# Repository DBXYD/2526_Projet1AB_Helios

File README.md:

# 2526_Projet1AB_Helios
Projet de 1ère année ENSEA sur un stroboscobe RGB
## Sommaire
* [Cahier des charges](#cahier-des-charges)
* [Matériels utilisés](#matériels-utilisés)
* [Organisation du projet](#organisation-du-projet)
  * [Architecture PCB](#architecture-pcb)
* [Journal de Bord du projet](#journal-de-bord-du-projet)
* [Répartition des Tâches](#répartition-des-tâches)
* [Membres du projet](#membres-du-projet)
## Cahier des charges
**Project scénique à LED**
* Strobe RGBW haute puissance (100 W minimum)
* Pilotage DMX512 (standard éclairage)
* interface utilisateur intuitive
* Modifier la fréquence d'allumage des LEDs
* Modes :
    * Intensité R/G/B
    * Strobe (fréquence, intensité)
* Sécurité thermique + électrique

**Contraintes**
* Alimentation secteur
* Fiabilité (usage scène)
* Dissipation thermique sérieuse
* Respect du DMX (isolation, timing)

## Présentation du projet
* [Présentation Hardware](https://github.com/DBXYD/2526_Projet1AB_Helios/blob/master/Presentation/Projet%201AB%20-%20H%C3%A9lios.pdf)
* [Architecture du Code](https://github.com/DBXYD/2526_Projet1AB_Helios/blob/master/Presentation/Projet1AB_Helios_Code.pdf) (DMX 512)

## Diagrammes
* [Diagrammes](https://github.com/DBXYD/2526_Projet1AB_Helios/tree/master/Presentation/Diagrammes)

## Matériels utilisés
| **Composant** | **Référence** |
| :-------- | :-------- |
| LEDs 98 (x3 couleurs) | [150505M173300](https://github.com/DBXYD/2526_Projet1AB_Helios/blob/master/datasheet/Datasheets%20du%20projet/LED_150505M173300.pdf) |
| 6 Driver | [LM3404](https://github.com/DBXYD/2526_Projet1AB_Helios/blob/master/datasheet/Datasheets%20du%20projet/lm3404.pdf) |
| Microcontrolleur | [STM32F103C6T6A LQFP-48](https://github.com/DBXYD/2526_Projet1AB_Helios/blob/master/datasheet/Datasheets%20du%20projet/stm32f103c6.pdf) |
| DMX512 | Mâle: [NC3MAAH](https://github.com/DBXYD/2526_Projet1AB_Helios/blob/master/datasheet/Datasheets%20du%20projet/nc3maah(DMX512M).pdf) Femelle: [NC3FAAH](https://github.com/DBXYD/2526_Projet1AB_Helios/blob/master/datasheet/Datasheets%20du%20projet/nc3faah(DMX512F).pdf) |
| Power Module WPME-FDSM | [173950536](https://github.com/DBXYD/2526_Projet1AB_Helios/blob/master/datasheet/Datasheets%20du%20projet/Power_Module_WPME-FDSM_173950536.pdf) |
| LOW DROPOUT LINEAR REGULATOR | [AZ1117CH2-TRG1](https://github.com/DBXYD/2526_Projet1AB_Helios/blob/master/datasheet/Datasheets%20du%20projet/AZ1117CH2-3.3TRG1.pdf) | 
| Ecran OLED | [OLED Dipslay](https://github.com/DBXYD/2526_Projet1AB_Helios/blob/master/datasheet/Datasheets%20du%20projet/SBC-OLED01_Datasheet_2022-01-06.pdf) |
| Alimentation | 24V / 5A | 
| Résistances | 2 x 1 kΩ ; 5 x 10 kΩ ; 2 x 1,6 kΩ ; 6 x 100 kΩ |
| Inductances | 6 x 18 uH |
| Condensateurs | 18 x 100 nF ; 2 x 1 uF ; 3 x 10 uF ; 1 x 22 uF ; 2 x 10 nF |
| LEDs SMD | 2 x [LED_0805_2012Metric](https://github.com/DBXYD/2526_Projet1AB_Helios/blob/master/datasheet/Datasheets%20du%20projet/LED_0805_2012Metric.pdf) |
| Boutons poussoirs | 3 x [Bouton ](https://github.com/DBXYD/2526_Projet1AB_Helios/blob/master/datasheet/Datasheets%20du%20projet/6x6_mm_sw_switches.pdf) |
| Puce MAX485E | [Puce](https://github.com/DBXYD/2526_Projet1AB_Helios/blob/master/datasheet/Datasheets%20du%20projet/MAX1487E-MAX491E.pdf) |
| Connecteur AMASS | [Connecteur 1](https://github.com/DBXYD/2526_Projet1AB_Helios/blob/master/datasheet/Datasheets%20du%20projet/XT30U-M_AMASS_Datasheet.pdf)|
| Connecteur PinHeader | [Connecteur 2](https://github.com/DBXYD/2526_Projet1AB_Helios/blob/master/datasheet/Datasheets%20du%20projet/connecteur%20pinheader.pdf)|

## Organisation du projet

### Architecture PCB:
* **Alimentation** : Power Module WPME-FSDM, AZ1117CH2-TRG1
* **Contrôle** : Microcontrolleur avec interface OLED
* **Pilotage LEDs** : drivers pour les chaînes R, G, B (2 drivers par couleur)
* **Protection et sécurité** : TODO (fusible, dissipateurs thermiques, diode)

### BOM:
[Matériel utilisé](https://github.com/DBXYD/2526_Projet1AB_Helios/blob/master/Hardware/KICAD_HELIOS/bom/ibom.html)

## Journal de Bord du projet 
[Journal de Bord](https://github.com/DBXYD/2526_Projet1AB_Helios/blob/master/journal_de_bord.md)

## Répartition des Tâches
| **Nom Prénom** | **Tâche(s)** |
| :-------- | :-------- |
| **TRITON Kylian** | Schématique du PCB, Routage du PCB, Valeurs des composants (fichier python), Mise à jour du Github, Recherche des composants |
| **RIEU Pierric** | Software des drivers (intégralité des codes), PCB |
| **BAILLEUL Sara** | Soudage, Vérification des empreintes sur PCB, Commande des composants et bon de commande du PCB, Recherche des composants (soudage et datasheet), Mise à jour du GitHub, Diagramme Hardware |
| **LEIRAS Clara** | LEDs (Schématique du PCB), Soudage, Recherche des composants (datasheet) |
| **GOMRI Samuel** | Recherche des composants |

## Membres du projet
|   |   |   |   |   |
|:---:|:---:|:---:|:---:|:---:|
|  |  |  |  |  | 
| [**@TritonKylian**](https://github.com/TritonKylian)<br>TRITON Kylian| [**@PierricRieu**](https://github.com/PierricRieu)<br>RIEU Pierric | [**@sblikeice**](https://github.com/sblikeice)<br> BAILLEUL Sara | [**@claralrs9**](https://github.com/claralrs9)<br>LEIRAS Clara| [**@sgomri**](https://github.com/sgomri)<br>GOMRI Samuel |

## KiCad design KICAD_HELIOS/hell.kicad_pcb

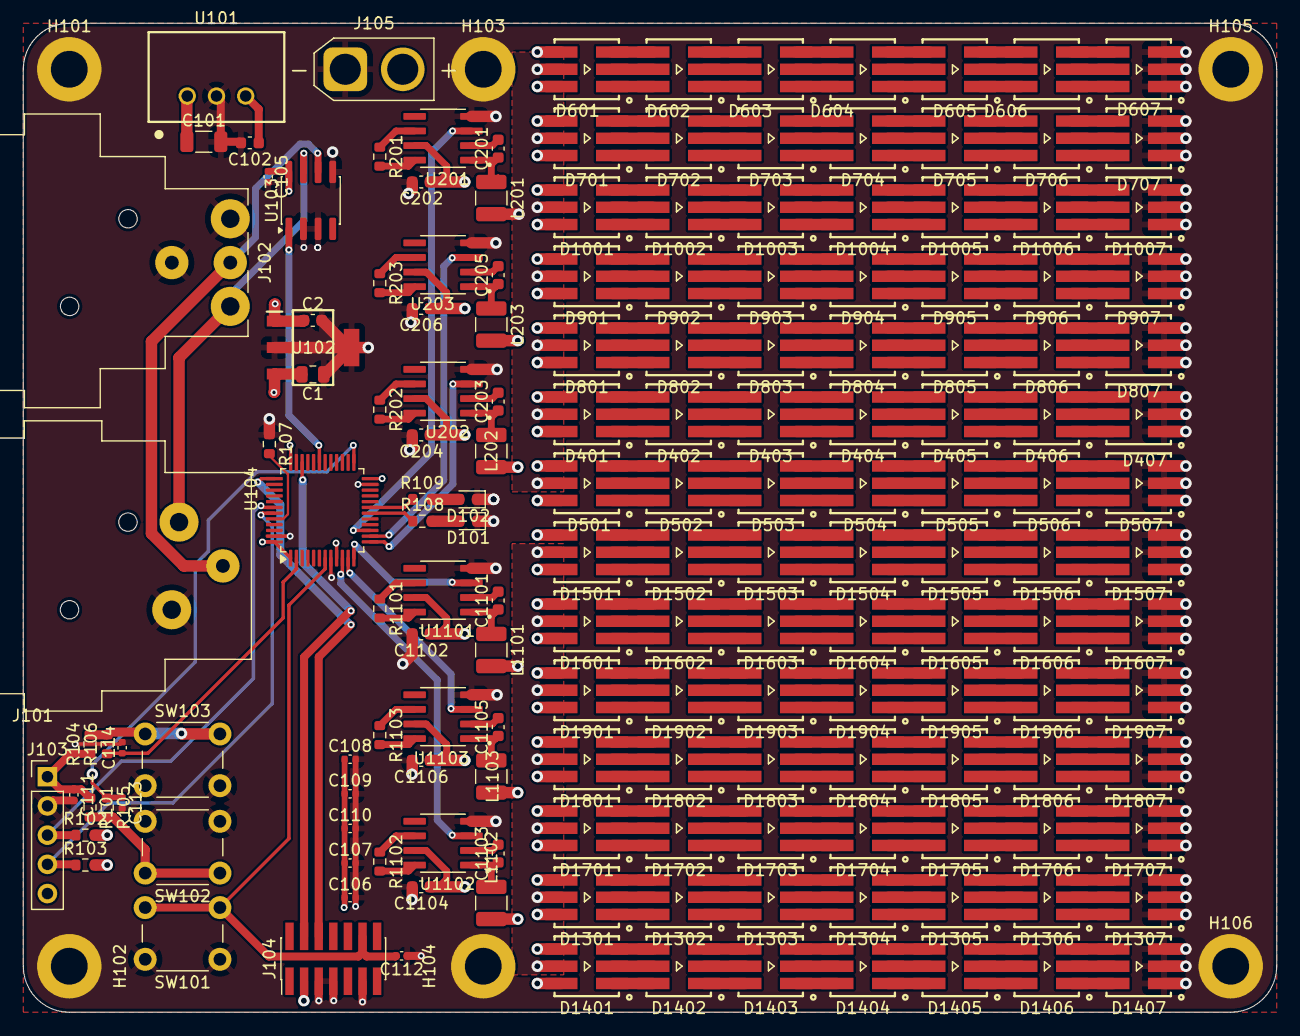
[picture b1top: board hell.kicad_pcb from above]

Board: 4 copper layers, 109.0 x 86.0 mm, 171 parts (0 on the bottom side), 309 nets.

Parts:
C1: 22u; C_0805_2012Metric
C2, C102: 10u; C_0603_1608Metric
C101: 10u; C_1206_3216Metric
C105, C107, C108, C109, C110, C112: 100n; C_0402_1005Metric
C106, C111: 1u; C_0402_1005Metric
C113, C114: 10n; C_0402_1005Metric
C201, C202, C203, C204, C205, C206, C1101, C1102, C1103, C1104, C1105, C1106: 100n; C_0603_1608Metric
D101, D102: LED; LED_0603_1608Metric
D401, D402, D403, D404, D405, D406, D407, D501, D502, D503, D504, D505, D506, D507, D601, D602, D603, D604, D605, D606, D607, D701, D702, D703, D704, D705, D706, D707, D801, D802, D803, D804, D805, D806, D807, D901, D902, D903, D904, D905, D906, D907, D1001, D1002, D1003, D1004, D1005, D1006, D1007, D1301, D1302, D1303, D1304, D1305, D1306, D1307, D1401, D1402, D1403, D1404, D1405, D1406, D1407, D1501, D1502, D1503, D1504, D1505, D1506, D1507, D1601, D1602, D1603, D1604, D1605, D1606, D1607, D1701, D1702, D1703, D1704, D1705, D1706, D1707, D1801, D1802, D1803, D1804, D1805, D1806, D1807, D1901, D1902, D1903, D1904, D1905, D1906, D1907: WL-SFTW_5050_PLCC6
H101, H102, H103, H104, H105, H106: MountingHole_Pad; MountingHole_3.2mm_M3_DIN965_Pad
J101: NC3FAAH; Jack_XLR_Neutrik_NC3FAAH_Horizontal
J102: NC3MAAH; Jack_XLR_Neutrik_NC3MAAH_Horizontal
J103: ecran; PinHeader_1x05_P2.54mm_Vertical
J104: Conn_ST_STDC14; PinHeader_2x07_P1.27mm_Vertical_SMD
J105: Conn_01x02; AMASS_XT30U-M_1x02_P5.0mm_Vertical
L201, L202, L203, L1101, L1102, L1103: 18u; L_1210_3225Metric
R101, R104, R105, R106, R107: 10k; R_0603_1608Metric
R102, R103: 1k; R_0603_1608Metric
R108, R109: 1k6; R_0603_1608Metric
R201, R202, R203, R1101, R1102, R1103: 100k; R_0603_1608Metric
SW101, SW102, SW103: SW_Push; SW_PUSH_6mm
U101: R-78B5.0-2.0; WPME-FDSM_173950536
U102: AZ1117CH2-3.3TRG1; SOT230P700X180-4N
U103: MAX485E; SOIC-8_3.9x4.9mm_P1.27mm
U104: STM32F103C6Tx; LQFP-48_7x7mm_P0.5mm
U201, U202, U203, U1101, U1102, U1103: LM3404MA; SOIC127P599X175-8N

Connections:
+3.3V: C1.2, C106.1, C107.1, C108.1, C109.1, C110.1, C111.1, J103.1, J104.3 (VCC), R101.1, R102.2, R103.2, R104.1, U102.3 (OUTPUT), U104.1 (VBAT), U104.9 (VDDA), U104.24 (VDD), U104.36 (VDD), U104.48 (VDD)
+5V: C2.1, C102.1, C105.1, U101.3, U102.1 (INPUT), U103.8 (VCC)
+24V: C101.1, C202.1, C204.1, C206.1, C1102.1, C1104.1, C1106.1, J105.2, U101.1, U201.7 (VCC), U202.7 (VCC), U203.7 (VCC), U1101.7 (VCC), U1102.7 (VCC), U1103.7 (VCC)
/Driver_49LED_RGB_1/B_49_Anode: D401.2, D501.2, D601.2, D701.2, D801.2, D901.2, D1001.2, L203.2
/Driver_49LED_RGB_1/G_49_Anode: D401.6, D501.6, D601.6, D701.6, D801.6, D901.6, D1001.6, L202.2
/Driver_49LED_RGB_1/R_49_Anode: D401.4, D501.4, D601.4, D701.4, D801.4, D901.4, D1001.4, L201.2
/Driver_49LED_RGB_2/B_49_Anode: D1301.2, D1401.2, D1501.2, D1601.2, D1701.2, D1801.2, D1901.2, L1103.2
/Driver_49LED_RGB_2/G_49_Anode: D1301.6, D1401.6, D1501.6, D1601.6, D1701.6, D1801.6, D1901.6, L1102.2
/Driver_49LED_RGB_2/R_49_Anode: D1301.4, D1401.4, D1501.4, D1601.4, D1701.4, D1801.4, D1901.4, L1101.2
BOUTTON_1: C114.1, R106.1, U104.2 (PC13)
BOUTTON_2: C113.1, R105.1, U104.25 (PB12)
DMX_N: J101.2, J102.2, U103.7 (B)
DMX_P: J101.3, J102.3, U103.6 (A)
DMX_RX: U103.1 (RO), U104.31 (PA10)
Ecr_SCL: J103.3, R102.1, U104.42 (PB6)
Ecr_SDA: J103.4, R103.1, U104.43 (PB7)
GND: C1.1, C2.2, C101.2, C102.2, C105.2, C106.2, C107.2, C108.2, C109.2, C110.2, C111.2, C112.1, C113.2, C114.2, C202.2, C204.2, C206.2, C1102.2, C1104.2, C1106.2, D101.1 (K), D102.1 (K), D407.1, D407.3, D407.5, D507.1, D507.3, D507.5, D607.1, D607.3, D607.5, D707.1, D707.3, D707.5, D807.1, D807.3, D807.5, D907.1, D907.3, D907.5, D1007.1, D1007.3, D1007.5, D1307.1, D1307.3, D1307.5, D1407.1, D1407.3, D1407.5, D1507.1, D1507.3, D1507.5, D1607.1, D1607.3, D1607.5, D1707.1, D1707.3, D1707.5, D1807.1, D1807.3, D1807.5, D1907.1, D1907.3, D1907.5, H101.1, H102.1, H103.1, H104.1, H105.1, H106.1, J101.1, J102.1, J102.G, J103.2, J104.5 (GND), J104.7 (GND), J104.11 (GNDDetect), J105.1, R107.1, SW101.1, SW102.2, SW103.2, U101.2, U102.2 (ADJ/GND_1), U102.4 (ADJ/GND_2), U103.2 (~RE), U103.3 (DE), U103.5 (GND), U104.8 (VSSA), U104.23 (VSS), U104.35 (VSS), U104.47 (VSS), U201.4 (GND), U202.4 (GND), U203.4 (GND), U1101.4 (GND), U1102.4 (GND), U1103.4 (GND)
LEDB1: U104.14 (PA4), U203.3 (DIM)
LEDB2: U104.11 (PA1), U1103.3 (DIM)
LEDG1: U104.13 (PA3), U202.3 (DIM)
LEDG2: U104.10 (PA0), U1102.3 (DIM)
LEDR1: U104.15 (PA5), U201.3 (DIM)
LEDR2: U104.12 (PA2), U1101.3 (DIM)
LED_1: R108.1, U104.18 (PB0)
LED_2: R109.1, U104.19 (PB1)
NRST: C112.2, J104.12 (~RST), SW101.2, U104.7 (NRST)
unnamed: D101.2 (A), R108.2
unnamed: D102.2 (A), R109.2
unnamed: D401.1, D402.2
unnamed: D401.3, D402.4
unnamed: D401.5, D402.6
unnamed: D402.1, D403.2
unnamed: D402.3, D403.4
unnamed: D402.5, D403.6
unnamed: D403.1, D404.2
unnamed: D403.3, D404.4
unnamed: D403.5, D404.6
unnamed: D404.1, D405.2
unnamed: D404.3, D405.4
unnamed: D404.5, D405.6
unnamed: D405.1, D406.2
unnamed: D405.3, D406.4
unnamed: D405.5, D406.6
unnamed: D406.1, D407.2
unnamed: D406.3, D407.4
unnamed: D406.5, D407.6
unnamed: D501.1, D502.2
unnamed: D501.3, D502.4
unnamed: D501.5, D502.6
unnamed: D502.1, D503.2
unnamed: D502.3, D503.4
unnamed: D502.5, D503.6
unnamed: D503.1, D504.2
unnamed: D503.3, D504.4
unnamed: D503.5, D504.6
unnamed: D504.1, D505.2
unnamed: D504.3, D505.4
unnamed: D504.5, D505.6
unnamed: D505.1, D506.2
unnamed: D505.3, D506.4
unnamed: D505.5, D506.6
unnamed: D506.1, D507.2
unnamed: D506.3, D507.4
unnamed: D506.5, D507.6
unnamed: D601.1, D602.2
unnamed: D601.3, D602.4
unnamed: D601.5, D602.6
unnamed: D602.1, D603.2
unnamed: D602.3, D603.4
unnamed: D602.5, D603.6
unnamed: D603.1, D604.2
unnamed: D603.3, D604.4
unnamed: D603.5, D604.6
unnamed: D604.1, D605.2
unnamed: D604.3, D605.4
unnamed: D604.5, D605.6
unnamed: D605.1, D606.2
unnamed: D605.3, D606.4
unnamed: D605.5, D606.6
unnamed: D606.1, D607.2
unnamed: D606.3, D607.4
unnamed: D606.5, D607.6
unnamed: D701.1, D702.2
unnamed: D701.3, D702.4
unnamed: D701.5, D702.6
unnamed: D702.1, D703.2
unnamed: D702.3, D703.4
unnamed: D702.5, D703.6
unnamed: D703.1, D704.2
unnamed: D703.3, D704.4
unnamed: D703.5, D704.6
unnamed: D704.1, D705.2
unnamed: D704.3, D705.4
unnamed: D704.5, D705.6
unnamed: D705.1, D706.2
unnamed: D705.3, D706.4
unnamed: D705.5, D706.6
unnamed: D706.1, D707.2
unnamed: D706.3, D707.4
unnamed: D706.5, D707.6
unnamed: D801.1, D802.2
unnamed: D801.3, D802.4
unnamed: D801.5, D802.6
unnamed: D802.1, D803.2
unnamed: D802.3, D803.4
unnamed: D802.5, D803.6
unnamed: D803.1, D804.2
unnamed: D803.3, D804.4
unnamed: D803.5, D804.6
unnamed: D804.1, D805.2
unnamed: D804.3, D805.4
unnamed: D804.5, D805.6
unnamed: D805.1, D806.2
unnamed: D805.3, D806.4
unnamed: D805.5, D806.6
unnamed: D806.1, D807.2
unnamed: D806.3, D807.4
unnamed: D806.5, D807.6
unnamed: D901.1, D902.2
unnamed: D901.3, D902.4
unnamed: D901.5, D902.6
unnamed: D902.1, D903.2
unnamed: D902.3, D903.4
unnamed: D902.5, D903.6
unnamed: D903.1, D904.2
unnamed: D903.3, D904.4
unnamed: D903.5, D904.6
unnamed: D904.1, D905.2
unnamed: D904.3, D905.4
unnamed: D904.5, D905.6
unnamed: D905.1, D906.2
unnamed: D905.3, D906.4
unnamed: D905.5, D906.6
unnamed: D906.1, D907.2
unnamed: D906.3, D907.4
unnamed: D906.5, D907.6
unnamed: D1001.1, D1002.2
unnamed: D1001.3, D1002.4
unnamed: D1001.5, D1002.6
unnamed: D1002.1, D1003.2
unnamed: D1002.3, D1003.4
unnamed: D1002.5, D1003.6
unnamed: D1003.1, D1004.2
unnamed: D1003.3, D1004.4
unnamed: D1003.5, D1004.6
unnamed: D1004.1, D1005.2
unnamed: D1004.3, D1005.4
unnamed: D1004.5, D1005.6
unnamed: D1005.1, D1006.2
unnamed: D1005.3, D1006.4
unnamed: D1005.5, D1006.6
unnamed: D1006.1, D1007.2
unnamed: D1006.3, D1007.4
unnamed: D1006.5, D1007.6
unnamed: D1301.1, D1302.2
unnamed: D1301.3, D1302.4
unnamed: D1301.5, D1302.6
unnamed: D1302.1, D1303.2
unnamed: D1302.3, D1303.4
unnamed: D1302.5, D1303.6
unnamed: D1303.1, D1304.2
unnamed: D1303.3, D1304.4
unnamed: D1303.5, D1304.6
unnamed: D1304.1, D1305.2
unnamed: D1304.3, D1305.4
unnamed: D1304.5, D1305.6
unnamed: D1305.1, D1306.2
unnamed: D1305.3, D1306.4
unnamed: D1305.5, D1306.6
unnamed: D1306.1, D1307.2
unnamed: D1306.3, D1307.4
unnamed: D1306.5, D1307.6
unnamed: D1401.1, D1402.2
unnamed: D1401.3, D1402.4
unnamed: D1401.5, D1402.6
unnamed: D1402.1, D1403.2
unnamed: D1402.3, D1403.4
unnamed: D1402.5, D1403.6
unnamed: D1403.1, D1404.2
unnamed: D1403.3, D1404.4
unnamed: D1403.5, D1404.6
unnamed: D1404.1, D1405.2
unnamed: D1404.3, D1405.4
unnamed: D1404.5, D1405.6
unnamed: D1405.1, D1406.2
unnamed: D1405.3, D1406.4
unnamed: D1405.5, D1406.6
unnamed: D1406.1, D1407.2
unnamed: D1406.3, D1407.4
unnamed: D1406.5, D1407.6
unnamed: D1501.1, D1502.2
unnamed: D1501.3, D1502.4
unnamed: D1501.5, D1502.6
unnamed: D1502.1, D1503.2
unnamed: D1502.3, D1503.4
unnamed: D1502.5, D1503.6
unnamed: D1503.1, D1504.2
unnamed: D1503.3, D1504.4
unnamed: D1503.5, D1504.6
unnamed: D1504.1, D1505.2
unnamed: D1504.3, D1505.4
unnamed: D1504.5, D1505.6
unnamed: D1505.1, D1506.2
unnamed: D1505.3, D1506.4
unnamed: D1505.5, D1506.6
unnamed: D1506.1, D1507.2
unnamed: D1506.3, D1507.4
unnamed: D1506.5, D1507.6
unnamed: D1601.1, D1602.2
unnamed: D1601.3, D1602.4
unnamed: D1601.5, D1602.6
unnamed: D1602.1, D1603.2
unnamed: D1602.3, D1603.4
unnamed: D1602.5, D1603.6
unnamed: D1603.1, D1604.2
unnamed: D1603.3, D1604.4
unnamed: D1603.5, D1604.6
unnamed: D1604.1, D1605.2
unnamed: D1604.3, D1605.4
unnamed: D1604.5, D1605.6
unnamed: D1605.1, D1606.2
unnamed: D1605.3, D1606.4
unnamed: D1605.5, D1606.6
unnamed: D1606.1, D1607.2
unnamed: D1606.3, D1607.4
unnamed: D1606.5, D1607.6
unnamed: D1701.1, D1702.2
unnamed: D1701.3, D1702.4
unnamed: D1701.5, D1702.6
unnamed: D1702.1, D1703.2
unnamed: D1702.3, D1703.4
unnamed: D1702.5, D1703.6
unnamed: D1703.1, D1704.2
unnamed: D1703.3, D1704.4
unnamed: D1703.5, D1704.6
unnamed: D1704.1, D1705.2
unnamed: D1704.3, D1705.4
unnamed: D1704.5, D1705.6
unnamed: D1705.1, D1706.2
unnamed: D1705.3, D1706.4
unnamed: D1705.5, D1706.6
unnamed: D1706.1, D1707.2
unnamed: D1706.3, D1707.4
unnamed: D1706.5, D1707.6
unnamed: D1801.1, D1802.2
unnamed: D1801.3, D1802.4
unnamed: D1801.5, D1802.6
unnamed: D1802.1, D1803.2
unnamed: D1802.3, D1803.4
unnamed: D1802.5, D1803.6
unnamed: D1803.1, D1804.2
unnamed: D1803.3, D1804.4
unnamed: D1803.5, D1804.6
unnamed: D1804.1, D1805.2
unnamed: D1804.3, D1805.4
unnamed: D1804.5, D1805.6
unnamed: D1805.1, D1806.2
unnamed: D1805.3, D1806.4
unnamed: D1805.5, D1806.6
unnamed: D1806.1, D1807.2
unnamed: D1806.3, D1807.4
unnamed: D1806.5, D1807.6
unnamed: D1901.1, D1902.2
unnamed: D1901.3, D1902.4
unnamed: D1901.5, D1902.6
unnamed: D1902.1, D1903.2
unnamed: D1902.3, D1903.4
unnamed: D1902.5, D1903.6
unnamed: D1903.1, D1904.2
unnamed: D1903.3, D1904.4
unnamed: D1903.5, D1904.6
unnamed: D1904.1, D1905.2
unnamed: D1904.3, D1905.4
unnamed: D1904.5, D1905.6
unnamed: D1905.1, D1906.2
unnamed: D1905.3, D1906.4
unnamed: D1905.5, D1906.6
unnamed: D1906.1, D1907.2
unnamed: D1906.3, D1907.4
unnamed: D1906.5, D1907.6
unnamed: R101.2, R105.2, SW102.1
unnamed: R104.2, R106.2, SW103.1
unnamed: R107.2, U104.44 (BOOT0)
unnamed: C201.2, U201.2 (BOOT)
unnamed: R201.1, U201.6 (RON)
unnamed: C201.1, L201.1, U201.1 (SW)
unnamed: R201.2, U201.8 (VIN)
unnamed: C203.2, U202.2 (BOOT)
unnamed: R202.1, U202.6 (RON)
unnamed: C203.1, L202.1, U202.1 (SW)
unnamed: R202.2, U202.8 (VIN)
unnamed: C205.2, U203.2 (BOOT)
unnamed: R203.1, U203.6 (RON)
unnamed: C205.1, L203.1, U203.1 (SW)
unnamed: R203.2, U203.8 (VIN)
unnamed: C1101.2, U1101.2 (BOOT)
unnamed: R1101.1, U1101.6 (RON)
unnamed: C1101.1, L1101.1, U1101.1 (SW)
unnamed: R1101.2, U1101.8 (VIN)
unnamed: C1103.2, U1102.2 (BOOT)
unnamed: R1102.1, U1102.6 (RON)
unnamed: C1103.1, L1102.1, U1102.1 (SW)
unnamed: R1102.2, U1102.8 (VIN)
unnamed: C1105.2, U1103.2 (BOOT)
unnamed: R1103.1, U1103.6 (RON)
unnamed: C1105.1, L1103.1, U1103.1 (SW)
unnamed: R1103.2, U1103.8 (VIN)
SWCLK: J104.6 (JCLK/SWCLK), U104.37 (PA14)
SWDIO: J104.4 (JTMS/SWDIO), U104.34 (PA13)

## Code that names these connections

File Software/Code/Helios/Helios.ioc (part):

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Mcu.Name=STM32F103C(4-6)Tx
Mcu.Package=LQFP48
Mcu.UserName=STM32F103C6Tx
PA0-WKUP.GPIOParameters=GPIO_Label
PA0-WKUP.GPIO_Label=LedR1
PA0-WKUP.Signal=S_TIM2_CH1_ETR
PA1.GPIOParameters=GPIO_Label
PA1.GPIO_Label=LedG1
PA1.Signal=S_TIM2_CH2
PA10.Mode=Asynchronous
PA10.Signal=USART1_RX
PA13.Signal=SYS_JTMS-SWDIO
PA14.Signal=SYS_JTCK-SWCLK
PA2.GPIOParameters=GPIO_Label
PA2.GPIO_Label=LedB1
PA2.Signal=S_TIM2_CH3
PA3.GPIOParameters=GPIO_Label
PA3.GPIO_Label=LedR2
PA3.Signal=S_TIM2_CH4
PA4.GPIOParameters=GPIO_Label
PA4.GPIO_Label=LedG2
PA4.Signal=GPIO_Output
PA5.GPIOParameters=GPIO_Label
PA5.GPIO_Label=LedB2
PA5.Signal=GPIO_Output
PA9.Mode=Asynchronous
PA9.Signal=USART1_TX
PB0.GPIOParameters=GPIO_Label
PB0.GPIO_Label=LED1
PB0.Signal=GPIO_Output
PB1.GPIOParameters=GPIO_Label
PB1.GPIO_Label=LED2
PB1.Signal=GPIO_Output
PB12.GPIOParameters=GPIO_Label
PB12.GPIO_Label=Boutton2
PB12.Signal=GPIO_Input
PC13-TAMPER-RTC.GPIOParameters=GPIO_Label
PC13-TAMPER-RTC.GPIO_Label=Boutton1
PC13-TAMPER-RTC.Signal=GPIO_Input
board=custom

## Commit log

2026-02-02 Update README with team member names
    Added team member names to the README.
2026-02-02 cahier des charges
2026-02-02 Add first session notes and project choice
2026-02-02 Update README.md
    Erreur sur la description du strobe
2026-02-02 Ajout du fichier dataset
2026-02-02 Ajout du dossier datasheet
2026-02-02 Suppression de l'ancien dossier dataset
2026-02-02 création d'un dossier code
2026-02-02 Création Hardware
2026-02-09 Add the datasheet file of the LED driver
    The only LED driver directly available at school
2026-02-09 choix de la LED
2026-02-09 Add files via upload
    Ecran OLED
2026-02-09 AJout du connecteur DMX512MALE
2026-02-09 Ajout du DMX512Female
2026-02-11 Revise README with project details and tasks
    Updated project description, added components with references and quantities, and revised task distribution.
2026-02-16 Datasheet for the Buck step down
    We use a Buck to go from 24V to 5V because a FDO would be inefficient and would disperse more heat.
2026-02-16 Rename non utilisée.pdf to LED_150505M173300.pdf
2026-02-16 add the datasheet for MAX485
2026-02-16 upload of the PDO's Datasheet
2026-02-16 Update component references in README
2026-02-16 Version PCB - non utilisée
2026-02-16 création du dossier kicad et ajout de la version sans led et drivers
2026-02-16 Ajout d'un fichier Kicad
2026-02-18 schématique combiné
2026-02-18 correction
2026-02-18 correctionV2
2026-02-18 Fix: correction erreurs schéma, maj empreintes et ajout notes
    - Résolution de toutes les erreurs ERC du schéma.
    - Mise à jour des empreintes (Importation d'empreintes non présentes dans KiCad, composants passifs...).
    - Ajout de Warning_KiCad_fichier_temporaire.md : liste des questions et problèmes à régler.
2026-02-18 Update status to include full schematic validation
2026-02-19 correction bug lié aux empreinte (dossier composant mit dans kicad)
2026-02-19 changement à faire schématic
2026-03-09 correction (reste à calculer L)
2026-03-09 schématic finie
2026-03-09 schematic + empreinte
2026-03-09 Update README with project summary and materials updated
2026-03-09 organisation routage
2026-03-16 PCB Routage 1ver
2026-03-16 update pcb
2026-03-16 Liste des composants
2026-03-16 Kicad PCB et changement de quelques empreintes
2026-03-30 Routage presque fini en attente de modification d'empreinte
2026-03-30 Routage PCB en prenant en compte la place mécanique des composants
2026-04-13 pcb pour impression
2026-04-13 Update journal_de_bord.md
    Déroulé des séances
2026-05-06 bonne datasheet pour la LED
2026-05-11 Réorganisation des fichiers et Mis à jour du Github
2026-05-11 Rename some files
2026-05-11 ajout du code
2026-05-11 Fix typo in inductance unit from uF to uH
2026-05-16 Régoranisation des datasheets
2026-05-16 Add files via upload
    bouton poussoir
2026-05-16 dossier présentation
2026-05-16 Présentation code
2026-05-18 présentation hardware
2026-05-18 modification readme
2026-05-18 modif composants
2026-05-18 changement datasheet
2026-05-18 code V2
2026-05-19 Modification du Read.me
2026-05-22 diagramme Hardware
